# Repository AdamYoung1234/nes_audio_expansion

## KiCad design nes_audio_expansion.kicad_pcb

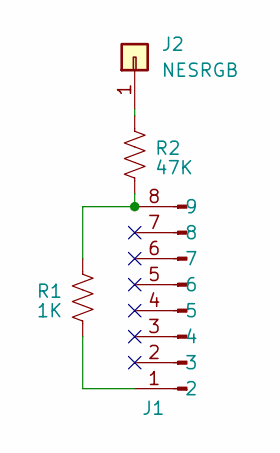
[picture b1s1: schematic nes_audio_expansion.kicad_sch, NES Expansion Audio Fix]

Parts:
J1: Expansion_Port; PinHeader_1x08_P2.54mm_Vertical
J2: NESRGB; TestPoint_Pad_1.5x1.5mm
R1: 1K; R_0805_2012Metric
R2: 47K; R_0805_2012Metric

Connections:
unnamed: J1.1 (2), R1.2
unnamed: J1.8 (9), R1.1, R2.2
unnamed: J2.1, R2.1

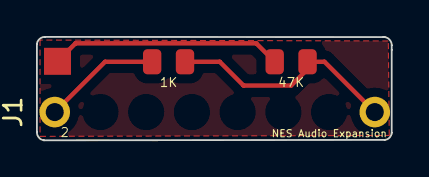
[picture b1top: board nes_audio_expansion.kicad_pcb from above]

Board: 2 copper layers, 19.7 x 5.7 mm, 4 parts (0 on the bottom side), 3 nets.

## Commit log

2023-07-25 added copper fill
